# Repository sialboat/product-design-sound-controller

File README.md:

# product-design-sound-controller
GitHub repository for my F25 Product Design project which aims to create a game controller that interfaces with MIDI-CC, CV, MPE, and as a Keyboard/Xbox Controller (so you can sound deisgn whilst playing games, of course)

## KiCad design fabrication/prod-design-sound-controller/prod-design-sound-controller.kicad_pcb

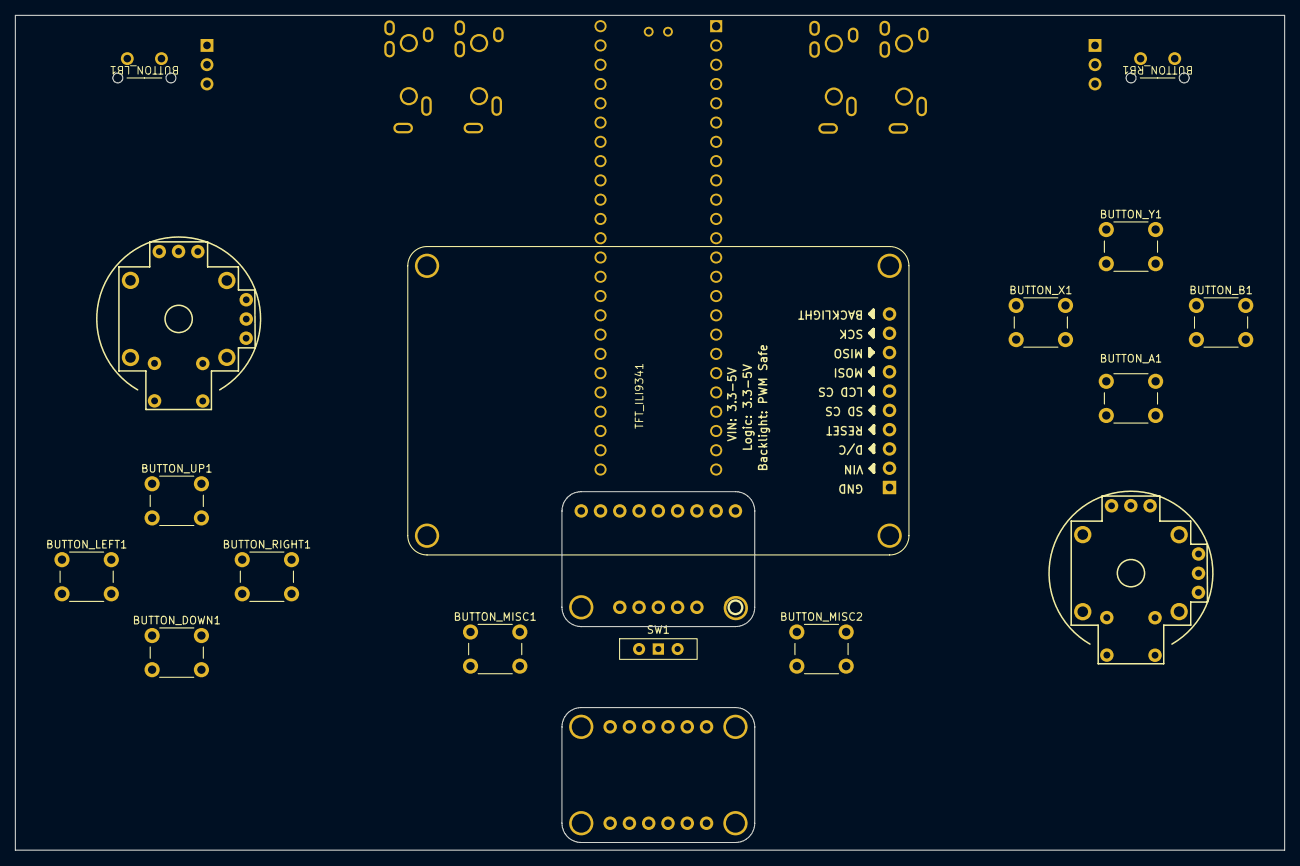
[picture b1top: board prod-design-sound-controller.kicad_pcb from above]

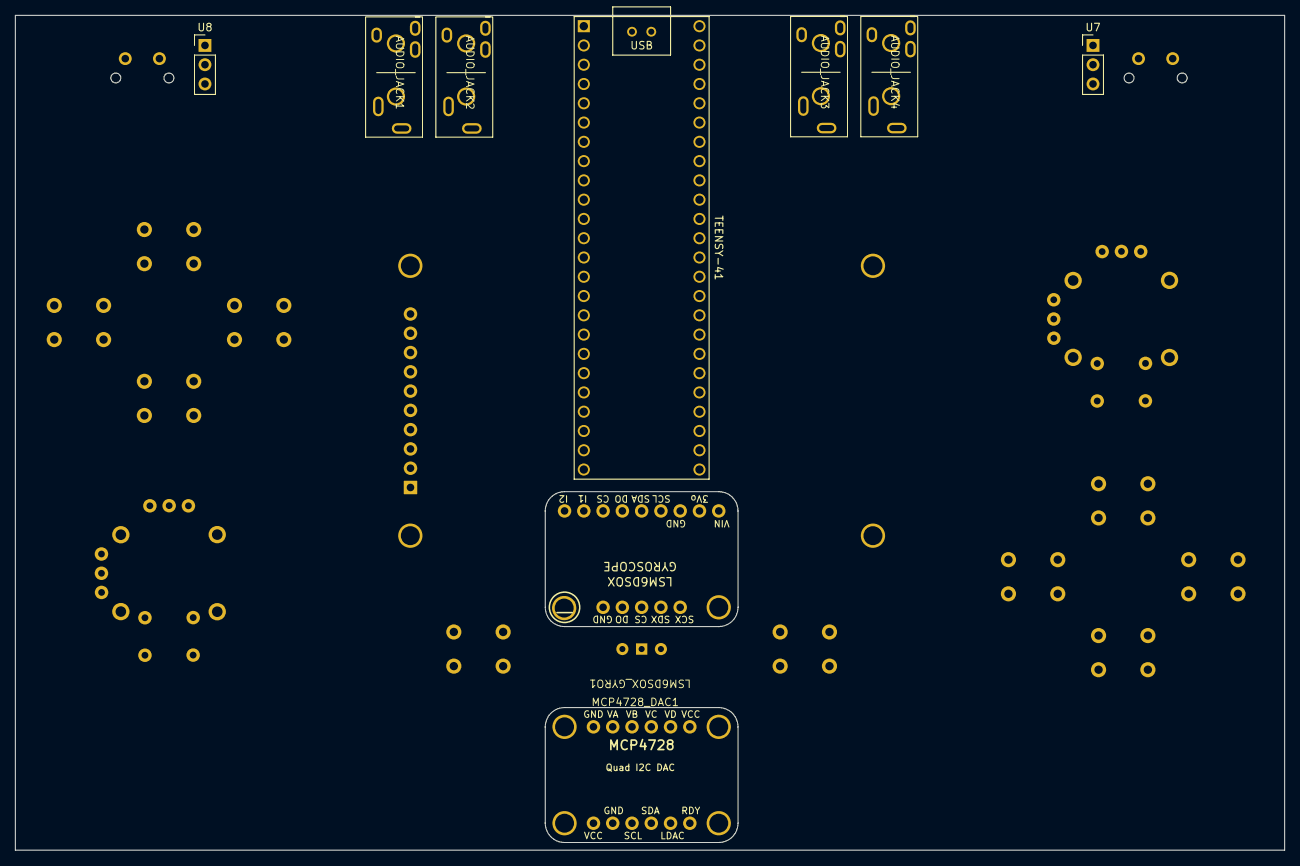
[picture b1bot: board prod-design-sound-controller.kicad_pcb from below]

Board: 2 copper layers, 167.2 x 110.0 mm, 25 parts (9 on the bottom side), 35 nets, no tracks yet.

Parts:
AUDIO_JACK1: CV_OUT_1; Audio_Jack
AUDIO_JACK2: CV_OUT_2; Audio_Jack
AUDIO_JACK3: CV_OUT_3; Audio_Jack
AUDIO_JACK4: CV_OUT_4; Audio_Jack
BUTTON_A1: SW_Push; SW_PUSH_6mm
BUTTON_B1: SW_Push; SW_PUSH_6mm
BUTTON_DOWN1: SW_Push; SW_PUSH_6mm
BUTTON_LB1: SW_Push; KIYOKOS-90Button
BUTTON_LEFT1: SW_Push; SW_PUSH_6mm
BUTTON_MISC1, BUTTON_MISC2: SW_Push; SW_PUSH_6mm
BUTTON_RB1: SW_Push; KIYOKOS-90Button
BUTTON_RIGHT1: SW_Push; SW_PUSH_6mm
BUTTON_UP1: SW_Push; SW_PUSH_6mm
BUTTON_X1: SW_Push; SW_PUSH_6mm
BUTTON_Y1: SW_Push; SW_PUSH_6mm
LEFT_JOYSTICK1: PS4_joystick
LSM6DSOX_GYRO1: LSM6DSOX_GYRO
MCP4728_DAC1: MCP4728_DAC
RIGHT_JOYSTICK1: PS4_joystick
SW1: BYPASS-SWITCH; SW_Slide-03_Wuerth-WS-SLTV_10x2.5x6.4_P2.54mm
TEENSY-41: Teensy4.1; Teensy41-prod-design
TFT_ILI9341: ILI9341_TFT_DISPLAY
U7: LEFT-TRIGGER; PinHeader_1x03_P2.54mm_Vertical
U8: RIGHT-TRIGGER; PinHeader_1x03_P2.54mm_Vertical

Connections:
+3.3V: LEFT_JOYSTICK1.H3 (VCC), LEFT_JOYSTICK1.V3 (VCC), LSM6DSOX_GYRO1.1 (VCC), MCP4728_DAC1.1 (VCC), RIGHT_JOYSTICK1.H3 (VCC), RIGHT_JOYSTICK1.V3 (VCC), TEENSY-41.48 (VIN), TFT_ILI9341.2 (VCC)
BUTTON-A: BUTTON_A1.2, TEENSY-41.18 (26_A12_MOSI1)
BUTTON-B: BUTTON_B1.2, TEENSY-41.17 (25_A11_RX6_SDA2)
BUTTON-DOWN: BUTTON_DOWN1.2, TEENSY-41.23 (31_CTX3)
BUTTON-LB: BUTTON_LB1.2, TEENSY-41.9 (7_RX2_OUT1A)
BUTTON-LEFT: BUTTON_LEFT1.2, TEENSY-41.22 (30_CRX3)
BUTTON-MISC1: BUTTON_MISC1.2, TEENSY-41.10 (8_TX2_IN1)
BUTTON-MISC2: BUTTON_MISC2.2, TEENSY-41.11 (9_OUT1C)
BUTTON-RB: BUTTON_RB1.2, TEENSY-41.8 (6_OUT1D)
BUTTON-RIGHT: BUTTON_RIGHT1.2, TEENSY-41.21 (29_TX7)
BUTTON-UP: BUTTON_UP1.2, TEENSY-41.24 (32_OUT1B)
BUTTON-X: BUTTON_X1.2, TEENSY-41.20 (28_RX7)
BUTTON-Y: BUTTON_Y1.2, TEENSY-41.19 (27_A13_SCK1)
BYPASS-SWITCH: SW1.2 (B), TEENSY-41.3 (1_TX1_CTX2_MISO1)
CV-1: AUDIO_JACK1.T (TIP), MCP4728_DAC1.8 (VA)
CV-2: AUDIO_JACK2.T (TIP), MCP4728_DAC1.9 (VB)
CV-3: AUDIO_JACK3.T (TIP), MCP4728_DAC1.10 (VC)
CV-4: AUDIO_JACK4.T (TIP), MCP4728_DAC1.11 (VD)
GND: AUDIO_JACK1.S (SLEEVE), AUDIO_JACK2.S (SLEEVE), AUDIO_JACK3.S (SLEEVE), AUDIO_JACK4.S (SLEEVE), BUTTON_A1.1, BUTTON_B1.1, BUTTON_DOWN1.1, BUTTON_LB1.1, BUTTON_LEFT1.1, BUTTON_MISC1.1, BUTTON_MISC2.1, BUTTON_RB1.1, BUTTON_RIGHT1.1, BUTTON_UP1.1, BUTTON_X1.1, BUTTON_Y1.1, LEFT_JOYSTICK1.B2A (GND), LEFT_JOYSTICK1.G (GND-SHIELD), LEFT_JOYSTICK1.H1 (GND), LEFT_JOYSTICK1.V1 (GND), LSM6DSOX_GYRO1.3 (GND), MCP4728_DAC1.2 (GND), RIGHT_JOYSTICK1.B2A (GND), RIGHT_JOYSTICK1.G (GND-SHIELD), RIGHT_JOYSTICK1.H1 (GND), RIGHT_JOYSTICK1.V1 (GND), SW1.1 (A), TEENSY-41.1 (GND), TEENSY-41.47 (GND), TFT_ILI9341.1 (GND)
ILI9341-DISPLAY-CS: TEENSY-41.12 (10_CS_MQSR), TFT_ILI9341.6 (CS)
ILI9341-DISPLAY-DC: TEENSY-41.26 (34_RX8), TFT_ILI9341.3 (DC)
ILI9341-DISPLAY-MISO: TEENSY-41.14 (12_MISO_MQSL), TFT_ILI9341.8 (MISO)
ILI9341-DISPLAY-MOSI: TEENSY-41.13 (11_MOSI_CTX1), TFT_ILI9341.7 (MOSI)
ILI9341-DISPLAY-RST: TEENSY-41.25 (33_MCLK2), TFT_ILI9341.4 (RST)
ILI9341-DISPLAY-SCK: TEENSY-41.35 (13_SCK_LED), TFT_ILI9341.9 (SCK)
INTERRUPT-1: LSM6DSOX_GYRO1.8 (I1), TEENSY-41.28 (36_CS)
INTERRUPT-2: LSM6DSOX_GYRO1.9 (I2), TEENSY-41.29 (37_CS)
LEFT-JOY-SEL: LEFT_JOYSTICK1.B1A (SEL), TEENSY-41.4 (2_OUT2)
LEFT-JOY-X: LEFT_JOYSTICK1.H2 (XOUT), TEENSY-41.42 (20_A6_TX5_LRCLK1)
LEFT-JOY-Y: LEFT_JOYSTICK1.V2 (YOUT), TEENSY-41.43 (21_A7_RX5_BCLK1)
RIGHT-JOY-SEL: RIGHT_JOYSTICK1.B1A (SEL), TEENSY-41.5 (3_LRCLK2)
RIGHT-JOY-X: RIGHT_JOYSTICK1.H2 (XOUT), TEENSY-41.44 (22_A8_CTX1)
RIGHT-JOY-Y: RIGHT_JOYSTICK1.V2 (YOUT), TEENSY-41.45 (23_A9_CRX1_MCLK1)
WIRE1-SCL: LSM6DSOX_GYRO1.4 (SCL), MCP4728_DAC1.3 (SCL), TEENSY-41.41 (19_A5_SCL)
WIRE1-SDA: LSM6DSOX_GYRO1.5 (SDA), MCP4728_DAC1.4 (SDA), TEENSY-41.40 (18_A4_SDA)

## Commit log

2025-08-06 06 08 25 - added the current files i have
2025-10-14 remembered my password (14 Oct 25)
2025-10-15 Midterm project report
    check "midterm demo" folder for the source code that produced the nightmare as seen on television.
2025-11-11 2025-11-10 push
    Pushing to github for syncing purposes
2025-11-20 revision v3 of pcb includes proper display placement. Needs additional adjustment for trigger, button, and joystick placement.
2025-11-26 basic tinyusb test, transitioning to pio branch
2025-11-26 transitioning to pio
2025-11-26 platformio project (needs cleanup)
2025-12-11 final project commit day!
2025-12-19 added final documentation
2025-12-19 on the right branch this time
